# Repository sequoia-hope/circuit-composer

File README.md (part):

# circuit-composer

Board design as composition: chips are ingested once into verified, published packages, and
boards are built by combining them. It covers the stage between schematic and routing:
constraint definition and physical design planning. The full design is in
[`Circuit Composer — System Spec.md`](Circuit%20Composer%20—%20System%20Spec.md).

It sits between two sibling projects:

- **[Boardroom](../boardroom)** (formerly easy_pcb) runs a board from requirements to fab outputs with the
  `pcb-design` skill. Its phase-3 classification (`design/nets.csv`) imports into an intent file,
  and its worked example, easy2350, is the first annotated board here.
- **[ultraroute](../ultraroute)** is the router. It takes this project's output: a KiCad board
  with critical blocks placed, routed and locked, plus rules and cost grids.

## Status

- **Milestone 1, intent schema v0:** done. Rust types, a generated JSON Schema, a validator,
  and one real board annotated by hand (`boards/easy2350/`) that passes it.
- **Milestone 2, one buck end to end:** done, for the RP2350's core regulator, an on-chip buck
  with an external inductor and capacitors. That covers a generator, fast-tier verifier checks,
  a comparison against Raspberry Pi's reference layout, and the first package,
  `packages/rp2350` 0.1.0, published in this repository.
- **Milestone 3, router integration:** done on our side. The constraint compiler, the region
  check and a routed-board seam check are in place. easy2350, with its blocks locked, was routed
  by ultraroute and passes every check (`boards/easy2350/routed/`), with and without
  ultraroute's `--regions` reading the compiled regions.
- **Milestone 4, RP2350 package:** `packages/rp2350` 0.2.0. Core-regulator layouts for QFN-60
  and QFN-80 on 2 and 4 layers, all beating Raspberry Pi's on the same checker. Crystal, USB,
  QSPI flash, buttons and decoupling as intent blocks, mined from the design guide and both
  minimal boards. Pin tables for both variants, 27 cited rules (disputes kept), and the support
  parts by role. `ccomp check package` judges any board against the package by role. Both
  reference boards pass every hard check. easy2350 fails one: its USB pair runs over the
  +3V3 plane, not ground.
- **Milestone 5, floorplanner and composer:** in progress.
  - **Composer:** `ccomp compose` builds a board's circuit from package instances, the board's
    own parts and the nets joining them, with a binding per instance for `ccomp check package`.
    Recomposing the RP2350A minimal board (55 nets) and easy2350 (65) reproduces their netlists
    exactly.
  - **Packages:** three more, each ingested from its datasheet with cited rules: `mcp73831`
    (LiPo charger), `tlv62569` (2 A buck, with a buck intent block) and `lsm6dso` (IMU); and
    the bolt earring's chips, as that board wires them: `lgs4056h` (charger), `ncp730` (3.3 V
    LDO), `tps22913` (load switch), `usblc6` (USB ESD) and `lsm6ds3trc` (IMU). And the RP2350
    motor controller's (rev A), as that board wires them: `eg3113` (one half-bridge phase: the
    EGmicro gate driver with its BSC030N08NS5 MOSFETs, bootstrap and gate network; the datasheet
    is Chinese only, quoted in Chinese), `ina240` (inline phase current sensing across two 8 mΩ
    shunts) and `lm74700` (ideal diode with its MOSFET, USB VBUS into the motor bus).
  - **The bolt earring from blocks:** `boards/bolt-earring/compose.json` composes the whole
    board from those packages, the RP2350's, and recipes for its power path, power latch,
    button, long-press BOOTSEL reset, dividers, light sensor and LED zones. It equals the
    bolt's netlist net for net (192 nets, all 256 parts). `loose.json` leaves the MCU's pins to
    the pin solver, which places all 15 connections. The app's Circuit workspace solves and
    composes it in the browser, with the pins and recipe parameters editable, and the Board
    workspace floorplans the solved board as well as the drawn one.
  - **KiCad output:** `tools/compose_kicad.py` writes the schematic (a box per block, a net
    label per pin) and the board through easy_pcb's writer. ERC is clean, and the board's pad
    nets equal the composed nets.
  - **Floorplanner:** `ccomp floorplan` places every part by simulated annealing, using
    pad-to-pad wirelength, courtyard overlap, board area, block cohesion, decoupling hints,
    rigid generated layouts, connectors flush on an edge facing out, through-hole pads that
    block both sides, and separations taken from the packages' rules.
    - In easy2350's own outline it finds a legal placement with 13 % less wirelength than the
      person's (763 mm against 878; KiCad DRC: no courtyard, clearance or short findings), with
      the parts whose place is part of the design locked where the person put them: the headers,
      USB-C, SWD, the RP2350 and its core regulator, the buttons and the LEDs.
    - A footprint locked in the board (KiCad's lock) stays put: `ccomp floorplan` fixes it, and
      the app reads each part's lock from the board it opens and writes it back when it saves.
    - The demo board is in `boards/rp2350-battery/`: USB-C, a charger, load sharing, a buck,
      the RP2350 and an IMU. It composes and floorplans legally at 40 × 32 mm.
    - Regions in the spec hold blocks to the brief's floorplan: a `must` region keeps its
      blocks' and parts' courtyards inside a polygon, a `never` region keeps them out (with no
      members, every moving part but those it `except`s), on one side or both. Both are hard,
      like overlap: `ok` needs no region misses.
    - A rigid layout's tracks and vias keep other parts off them, as its parts do. A part keeps
      the margin from a side an edge connector sits flush on, and separations rise in weight
      through the anneal, like overlaps, so the end keeps them.
  - **Board intent:** `ccomp compose --intent` writes the composed board's intent file: each
    package's `intent.json` in board names (its nets found through their pins, its parts
    through the binding, blocks and domains named `INSTANCE/NAME`), nets two packages share
    merged to the stricter values, then the composition's own `intent` (board nets no package
    covers, a default for the rest). KiCad's net names, as `compose_kicad.py` labels them. The
    charger and IMU packages carry intent files now; the battery board's validates against its
    netlist, 42 of 42 nets.
  - **Routing composed boards:** `tools/prepare_route.py` gives a placed board its stack-up
    (4 layers), the fab rules, a net class per net from its intent, planes, a current-width rule
    where a net's current needs one (IPC-2221), and each rigid block's generated copper, locked.
    `tools/route_board.sh` runs it all from the composition through ultraroute to the seam
    checks. The battery board routes in under a minute with 0 DRC errors, 0 unconnected and 0
    region violations on 4 of 4 seeds (`boards/rp2350-battery/routed/`).
  - **Package rules as routing constraints:** `ccomp compile` turns the packages' block
    constraints into regions: `via_count <= 0` into a via rule, `unreferenced_length_mm <= 0`
    into keeping off layers with no ground beside them and off the voids in the ground fill
    beside the others. Hard constraints are `never`, soft ones a weighted `avoid`. `ccomp floorplan
    --intent` keeps a length-limited net's pins' box under 0.75 of its limit. Against the
    rp2350 package the battery board went from 22 fails of 63 (2 hard) to 13 to 15, with no
    hard fail on any of 4 seeds.
  - **Decoupling:** `prepare_route.py --composed` draws and locks each decoupling capacitor's stub
    to its pin, and the floorplanner leaves room for it: a `near` hint is measured from the
    part's pad on that net, and other courtyards across the line to the pin are priced. The
    battery board's decoupling fails went from 6 to 1 to 3.
  - **Off-chip bucks:** `ccomp gen buck` places a divider (`rfb_top`, `rfb_bot`, `cff` roles: FB
    runs clear of the switch node, the VOUT sense from COUT when it fits), takes the output net
    from the inductor, can return ground through the plane (`gnd_return_vias`), and searches
    behind the switch pin's row (`back`). The TLV62569's layout (`packages/tlv62569/layouts/`)
    measures 3.53 mm² hot loop and 11.05 mm² output loop, and the battery board uses it: package
    fails 9 to 13 of 63, none hard, on 4 seeds (ultraroute f179fcb, which reads `clear_under`:
    other nets' vias keep their plane holes from under a hard over-ground net).
  - **Crossings:** `ccomp floorplan` can price crossings between the straight pin lines of the
    nets a block keeps over ground (`planar` from the intent, `w_cross`, off by default). On the
    battery board it took the QSPI fails from 8.25 to 7.0 on average over four placements, but
    the crystal's from 1.25 to 3.5 (`boards/rp2350-battery/routed/README.md`).
  - **Not yet:** room for every stub beside the chip (8 of 10 fit); the flash's QSPI over ground
    (soft in the rp2350 package, so the router pays its price);
    intent for the remaining packages and the recipes; package schematic sheets.
- **Research library:** `library/` holds 143 cited claims from 41 vendor app notes, datasheets
  and articles, on five topics:
  - buck layout,
  - half-bridges and motor drivers,
  - crystal oscillators,
  - USB, return paths and decoupling,
  - CAN, connector protection and trace current.

  It is one database with the packages' rules. 17 disputes are kept as linked pairs, one of
  them against an rp2350 rule. Every quote is checked against its document
  (`library/README.md`).

## The app (prototype)

`app/` is Circuit Composer's own UI, specified in [`docs/app-spec.md`](docs/app-spec.md): a Rust
core compiled to WASM (`app/core`, the floorplanner and the board document) and a Svelte page
(`app/web`). It opens a board's floorplan; you drag, rotate and lock parts, and the floorplanner
anneals live in a worker in the page, from scratch or refining what is there. The Circuit
workspace shows the board as blocks and the nets between them. Shape builds the board's
outline: rectangles, circles, slots, polygons and generators (the bolt earring's is the first),
each added or cut away, with corner rounding, symmetry, holes, keep-outs and SVG/DXF import;
"Use as board outline" hands it to the floorplanner. The geometry is `crates/shape`, also behind
`ccomp shape`, and a board's `shape.json` reaches `ccomp floorplan` when its spec sets no
outline. It runs with no server: it opens the example boards that
`app/examples.sh` exports from `boards/` into the site. That is also how it runs on GitHub Pages,
where the site is the app alone: <https://sequoia-hope.github.io/circuit-composer/>.
Boards are drawn through a placeholder until `board-draw`, the renderer shared with UltraRoute
Studio, lands. AI fills, the terminal and the handoff to UltraRoute need the app's server, which
is next.

```sh
app/examples.sh     # export boards/ as the app's example boards (committed)
app/build.sh        # core to WASM, page to app/dist/
./serve.sh          # then open /app/dist/ on the project's registered port
```

URL parameters: `board=NAME`, `view=circuit|board|shape|copper|rules` (`ws=` in older links),
`embed=1` (for Boardroom's single-window mode: a slim bar of workspaces and, for a project's board,
Save, in place of the header; selection is posted to the parent window). On a touchscreen a finger
pans the board and two pinch to zoom. With a mouse or a finger, a press on a part selects it, and
only a selected, unlocked part moves, once dragged past a few pixels; Esc during a drag puts it
back.

## Build and run

```sh
cargo build --release
ccomp=target/release/ccomp

$ccomp schema -o schema/intent.schema.json             # regenerate the JSON Schema
$ccomp classes                                         # net class presets and block types
$ccomp netlist path/to/board.kicad_sch                 # the netlist as JSON (runs kicad-cli)
$ccomp validate boards/easy2350/intent.json            # pass/fail, findings per net and block
$ccomp resolve boards/easy2350/intent.json             # nets with preset defaults filled in
$ccomp import easy-pcb ../boardroom/examples/easy2350/design/nets.csv \
    --board easy2350 --netlist ../boardroom/examples/easy2350/hw/easy2350/a/easy2350.kicad_sch \
    -o draft.json                                      # draft intent from Boardroom
```

Any command can work on a board in a project instead of being given every path:
`--project DIR` (`-C`) and `--board NAME` (`-b`) fill in the inputs it was not given from the
board's files. Boards live under `compose/<board>/` in a Boardroom project and under
`boards/<board>/` here, each optionally with a `board.json` naming where its files are
(`crates/ccomp/src/project.rs`). Outputs are still written only with `-o`.

```sh
$ccomp boards                                          # this repository's boards
$ccomp -b rp2350-battery boards                        # one board's files, and which exist
$ccomp -b rp2350-battery compose                       # = compose boards/rp2350-battery/compose.json
$ccomp -C ../my-project floorplan --seed 2             # a project's only board
```

Milestone 2's tools:

```sh
# Fast-tier checks on a buck block, with a picture of what was measured
$ccomp check buck board.kicad_pcb --roles vin=U1.49,sw=U1.48,pgnd=U1.47,fb=U1.50,cin=C6,cout=C7,inductor=L1 --svg block.svg
$ccomp check buck board.kicad_pcb --intent boards/easy2350/intent.json --block core_reg

# Generate the block (parts and copper in the IC's frame); --defaults prints the parameters
$ccomp gen buck board.kicad_pcb --intent boards/easy2350/intent.json --block core_reg -o gen.json

# Generate, apply to a test bench with pcbnew, verify, and run KiCad's DRC
~/.claude/bin/reserve -c 8 -l "buck bench" -- python3 tools/bench_buck.py BOARD ROLES.json OUT_DIR
python3 tools/apply_layout.py BOARD gen.json ROLES.json -o OUT.kicad_pcb [--group NAME] [--fixture]
# A vendor board's own regulator copper (parts, pours, joining tracks and vias) as a layout
python3 tools/extract_layout.py REFERENCE.kicad_pcb ROLES.json -o layout.json --source rp2350a_minimal
# Any reviewed cluster with no generator (a half-bridge cell, a BGA's decoupler field, bottom-side
# members included) lifted from a board as a rigid layout, plus roles.json beside it
python3 tools/lift_layout.py BOARD.kicad_pcb --anchor U501 --parts Q501 Q502 C510 -o DIR/layout.json [--roles ROLES.json]
python3 tools/compare_buck.py packages/rp2350/layouts/qfn60-4layer/compare.spec.json OUT_DIR
```

Milestone 4 adds net-level measurements, for interface blocks:

```sh
# Pad-to-pad copper paths, track with no ground beside it, nearest decoupling per power pin
$ccomp measure board.kicad_pcb --spec packages/rp2350/reference/rp2350a_minimal/measure.spec.json
python3 tools/kicad_pins.py board.net U1 --rename SWD=SWDIO   # a part's pin table from a netlist

# A board against a package, by role: wiring, block constraints, length limits, part values
$ccomp check package board.kicad_pcb --package packages/rp2350 --binding boards/easy2350/rp2350.binding.json
```

Composing and floorplanning (milestone 5):

```sh
python3 tools/circuit_check.py packages/*/schematic/circuit.*.json --kicad 9   # symbols, footprints, pins
$ccomp pins boards/rp2350-battery/loose.json -o compose.json                  # pins solved; a regulator for each rail named under rails with none
$ccomp check supplies boards/rp2350-battery/compose.json                       # each rail's range, budget and feeds, judged
$ccomp compose boards/rp2350-battery/compose.json -o composed.json --intent intent.json   # + the board's intent
python3 tools/compose_kicad.py composed.json OUT_DIR --easy-pcb ../boardroom    # schematic, ERC, board
$ccomp floorplan OUT_DIR/BOARD.kicad_pcb --composed composed.json --spec boards/rp2350-battery/floorplan.json -o placement.json
$ccomp floorplan ... --evaluate PLACED.kicad_pcb                               # score a person's placement
python3 tools/apply_placement.py OUT_DIR/BOARD.kicad_pcb placement.json -o placed.kicad_pcb   # + KiCad DRC
python3 tools/prepare_route.py placed.kicad_pcb --intent intent.json --spec boards/rp2350-battery/floorplan.json \
    --pro OUT_DIR/BOARD.kicad_pro -o ROUTE_IN                                  # stack-up, rules, classes, planes, locked blocks
ULTRAROUTE=PATH tools/route_board.sh rp2350-battery OUT [SEED]                 # all of it, routed and checked
```

Recomposing an existing board:

```sh
$ccomp compose boards/easy2350/compose.json -o composed.json --bindings OUT_DIR   # circuit + bindings
python3 tools/package_circuit.py packages/rp2350 --board qfn60 --variant RP2350A --netlist REF.net --chip U1 --source rp2350a_minimal -o packages/rp2350/schematic/circuit.RP2350A.json
python3 tools/compose_from_netlist.py draft BOARD.net --instance mcu rp2350@0.2.0 RP2350A BINDING.json --keep-designators -o compose.json
python3 tools/compose_from_netlist.py compare BOARD.net composed.json --binding mcu BINDING.json
```

The research library:

```sh
$ccomp library check                                   # ids, sources, links, both sides of each dispute
$ccomp library query --scope circuit=buck --status contested
python3 tools/library_fetch.py && python3 tools/library_quotes.py   # documents, hashes, quotes
```

Every command prints one JSON result. Exit status: 0 success, 1 the input failed validation,
2 the command could not run.

## Layout

| Path | What |
|---|---|
| `crates/intent/` | The schema types (`model.rs`), class presets and block types (`presets.rs`), the KiCad netlist reader, the validator, the easy_pcb importer |
| `crates/ccomp/` | The command-line harness |
| `crates/pcb/` | A KiCad board as copper per net (read with ultraroute's `kicad-pcb`, pinned), geometry, and copper-path search |
| `crates/verify/` | Fast-tier verifier checks (`buck.rs`, `nets.rs`) and SVG drawings of what they measured |
| `crates/floorplan/` | The floorplanner: simulated annealing over part poses, rigid groups, regions, edges, separations |
| `crates/compose/` | The composer: package instances, the board's own parts and nets into one circuit, with a binding per instance |
| `crates/library/` | The research library: cited claims from `library/` and every package's `rules.json`, checked and queried as one database |
| `crates/blockgen/` | Block generators (`buck.rs`) and the layout format, in the anchor part's frame |
| `tools/` | pcbnew-side steps: apply a layout, the test bench, comparisons |
| `library/` | Claims by circuit class, their sources (URLs and hashes; documents cached, not committed) |
| `packages/<chip>/` | Published packages: manifest, intent, cited rules, layouts with verify reports |
| `schema/intent.schema.json` | Generated; a test fails if it is stale |
| `boards/<board>/` | One annotated board each: `intent.json`, `input/` (netlist snapshot), `validate.json` |
| `.claude/skills/circuit-composer/` | The Claude Code skill that drives `ccomp` |

## The intent file (v0)

A JSON sidecar keyed by KiCad net names (`/GPIO0`, `+3V3`) and reference designators. Every
constrained value is `{value, strength: hard|soft, weight (soft only), provenance}`, and a
provenance cites a key of `sources` with a locator (page, section, timestamp) and a kind:
`datasheet`, `expert`, `simulated`, `requirement` (the board's own budget), or `preset`.

Net classes are presets over attributes: a class names the attributes a net must state (`SWITCH`
needs `voltage` and `current`) and supplies soft defaults for the rest (aggressor `strong`). A
default never satisfies a requirement and can never be hard.

The validator refuses a board until every connected net has intent with its class's required
fields, every block has a library type and owns real parts (no part in two blocks), every hard
constraint (including `must`/`never` region rules and protection paths) has a provenance that
resolves to a source, protection-path pads lie on their net, and differential pairs name each
other.

## Decisions

| Decision | Why |
|---|---|
| Intent file is JSON (spec open question) | The schema is generated as JSON Schema from the Rust types; packages already use `intent.json`; serde refuses unknown fields, so typos fail loudly |
| `requirement` and `preset` provenance kinds, beyond the spec's datasheet/expert/simulated | Board budgets (500 mA USB) are the designer's claims, not a datasheet's; presets must be visibly weaker than evidence |
| `max_length` net attribute, beyond the spec's table | easy_pcb's `length_limit` is enforced today and the router needs it |
| Regions may be anchored to a part | Package rules ("cut layer 2 under the inductor's LX pad") are stated relative to parts, before placement exists |
| Boards keep a netlist snapshot in `input/` | Validation is reproducible without the sibling checkout, as ultraroute's `jobs/<board>/input/` |

## Milestone 2: the RP2350 core regulator

**Checks** (`crates/verify/src/buck.rs`, about 1 s on a whole board). Copper paths are found
through tracks, vias and zone fills. Loop areas integrate |winding number|, so a loop that
crosses itself counts both lobes; a plain shoelace sum let them cancel and under-reported the
reference's output loop by half.

| Check | What |
|---|---|
| `hot_loop_area_mm2` | VIN pin → CIN → PGND pin along the copper |
| `output_loop_area_mm2` | SW pin → inductor → COUT → PGND pin |
| `switch_node_area_mm2` | All switch-net copper, overlaps counted once |
| `feedback_clearance_mm` | Feedback path (FB pin to COUT) to switch-node copper, IC pins excluded |
| `switch_node_underlap_mm2` | Other nets' copper on the layer under the switch node |

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
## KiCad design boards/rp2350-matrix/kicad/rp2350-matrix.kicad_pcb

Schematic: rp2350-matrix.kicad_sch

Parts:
C1, C2, C20: 10u; C_0805_2012Metric; Mpn CL21A106KAYNNNE; LCSC C15850
C3, C8: 4.7u; C_0402_1005Metric
C4, C7: 4.7u; C_0402_1005Metric_small_pads
C5, C6: 15p; C_0402_1005Metric
C9, C10, C11, C12, C13, C14, C15, C16, C17, C18: 100n; C_0402_1005Metric
C19: 6.8p; C_0402_1005Metric; Mpn 0402CG6R8C500NT; LCSC C1576
C21: 22u; C_0805_2012Metric; Mpn CL21A226MAQNNNE; LCSC C45783
C101, C102, C103, C104, C105, C106, C107, C108, C109, C110, C111, C112, C113, C114, C115, C116: 100n; C_0402_1005Metric; Mpn CL05B104KO5NNNC; LCSC C1525
D1: RED; LED_0603_1608Metric; Mpn KT-0603R; LCSC C2286
D3: B5819W; D_SOD-123; LCSC C8598
J1: USB-C; USB_C_Receptacle_HRO_TYPE-C-31-M-12; LCSC C165948
J2: BATT; JST_PH_S2B-PH-SM4-TB_1x02-1MP_P2.00mm_Horizontal; LCSC C295747
J3: SWD; PinHeader_1x03_P2.54mm_Vertical
L1: 3.3u; L_pol_2016
L2: 2.2u; L_Sunlord_SWPA4020S; Mpn SMNR4020-2.2UH; LCSC C135262
LED1, LED2, LED3, LED4, LED5, LED6, LED7, LED8, LED9, LED10, LED11, LED12, LED13, LED14, LED15, LED16, LED17, LED18, LED19, LED20, LED21, LED22, LED23, LED24, LED25, LED26, LED27, LED28, LED29, LED30, LED31, LED32, LED33, LED34, LED35, LED36, LED37, LED38, LED39, LED40, LED41, LED42, LED43, LED44, LED45, LED46, LED47, LED48, LED49, LED50, LED51, LED52, LED53, LED54, LED55, LED56, LED57, LED58, LED59, LED60, LED61, LED62, LED63, LED64: WS2816C-1313; LED_WS2816C-1313; Mpn WS2816C-1313/4P; LCSC C42417612
Q1: AO3401A; SOT-23; LCSC C15127
Q2: BSS138W; SOT-323_SC-70; Mpn BSS138W-7-F-ES; LCSC C5224279
R1, R2: 5.1k; R_0402_1005Metric; LCSC C25905
R3: 100k; R_0402_1005Metric; LCSC C25741
R4: 4.7k; R_0402_1005Metric; Mpn 0402WGF4701TCE; LCSC C25900
R5: 1k; R_0402_1005Metric; Mpn 0402WGF1001TCE; LCSC C11702
R6: 470; R_0402_1005Metric; Mpn 0402WGF4700TCE; LCSC C25117
R7: 33; R_0402_1005Metric
R8, R10, R15: 1k; R_0402_1005Metric
R9, R12: DNF; R_0402_1005Metric
R11: 0; R_0402_1005Metric
R13, R14: 27; R_0402_1005Metric
R16: 100k; R_0402_1005Metric; Mpn 0402WGF1003TCE; LCSC C25741
R17: 453k; R_0402_1005Metric; Mpn 0402WGF4533TCE; LCSC C27009
R18: 1M; R_0402_1005Metric; Mpn 0402WGF1004TCE; LCSC C26083
SW1, SW2: SW_Push; SW_Push_1P1T_NO_Vertical_Wuerth_434133025816
U1: MCP73831T-2ACI/OT; SOT-23-5; Mpn MCP73831T-2ACI/OT; LCSC C424093
U2: W25Q128JVS; SOIC-8_5.3x5.3mm_P1.27mm
U3: RP2350_60QFN; RP2350-QFN-60-1EP_7x7_P0.4mm_EP3.4x3.4mm_ThermalVias
U4: TLV62569DBV; SOT-23-5; Mpn TLV62569DBVR; LCSC C141836
Y1: ABM8-272-T3; Crystal_SMD_3225-4Pin_3.2x2.5mm

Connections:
/CC1: J1.A5 (CC1), R1.1
/CC2: J1.B5 (CC2), R2.1
/LED_DATA: Q2.1 (G), U3.27 (GPIO16)
/LED_DIN: LED1.4 (DIN), Q2.3 (D), R5.2
/SWCLK: J3.1, U3.24 (SWCLK)
/SWDIO: J3.3, U3.25 (SWD)
/USB_D+: J1.A6 (D+), J1.B6 (D+), R14.1
/USB_D-: J1.A7 (D-), J1.B7 (D-), R13.1
/VBAT: C2.1, J2.1, Q1.3 (D), U1.3 (V_{BAT})
/chg_PROG: R4.1, U1.5 (PROG)
/chg_STAT: R6.2, U1.1 (STAT)
/chg_STAT_LED: D1.1 (K), R6.1
/leds_D1_DO: LED1.2 (DOUT), LED2.4 (DIN)
/leds_D2_DO: LED2.2 (DOUT), LED3.4 (DIN)
/leds_D3_DO: LED3.2 (DOUT), LED4.4 (DIN)
/leds_D4_DO: LED4.2 (DOUT), LED5.4 (DIN)
/leds_D5_DO: LED5.2 (DOUT), LED6.4 (DIN)
/leds_D6_DO: LED6.2 (DOUT), LED7.4 (DIN)
/leds_D7_DO: LED7.2 (DOUT), LED8.4 (DIN)
/leds_D8_DO: LED8.2 (DOUT), LED9.4 (DIN)
/leds_D9_DO: LED9.2 (DOUT), LED10.4 (DIN)
/leds_D10_DO: LED10.2 (DOUT), LED11.4 (DIN)
/leds_D11_DO: LED11.2 (DOUT), LED12.4 (DIN)
/leds_D12_DO: LED12.2 (DOUT), LED13.4 (DIN)
/leds_D13_DO: LED13.2 (DOUT), LED14.4 (DIN)
/leds_D14_DO: LED14.2 (DOUT), LED15.4 (DIN)
/leds_D15_DO: LED15.2 (DOUT), LED16.4 (DIN)
/leds_D16_DO: LED16.2 (DOUT), LED17.4 (DIN)
/leds_D17_DO: LED17.2 (DOUT), LED18.4 (DIN)
/leds_D18_DO: LED18.2 (DOUT), LED19.4 (DIN)
/leds_D19_DO: LED19.2 (DOUT), LED20.4 (DIN)
/leds_D20_DO: LED20.2 (DOUT), LED21.4 (DIN)
/leds_D21_DO: LED21.2 (DOUT), LED22.4 (DIN)
/leds_D22_DO: LED22.2 (DOUT), LED23.4 (DIN)
/leds_D23_DO: LED23.2 (DOUT), LED24.4 (DIN)
/leds_D24_DO: LED24.2 (DOUT), LED25.4 (DIN)
/leds_D25_DO: LED25.2 (DOUT), LED26.4 (DIN)
/leds_D26_DO: LED26.2 (DOUT), LED27.4 (DIN)
/leds_D27_DO: LED27.2 (DOUT), LED28.4 (DIN)
/leds_D28_DO: LED28.2 (DOUT), LED29.4 (DIN)
/leds_D29_DO: LED29.2 (DOUT), LED30.4 (DIN)
/leds_D30_DO: LED30.2 (DOUT), LED31.4 (DIN)
/leds_D31_DO: LED31.2 (DOUT), LED32.4 (DIN)
/leds_D32_DO: LED32.2 (DOUT), LED33.4 (DIN)
/leds_D33_DO: LED33.2 (DOUT), LED34.4 (DIN)
/leds_D34_DO: LED34.2 (DOUT), LED35.4 (DIN)
/leds_D35_DO: LED35.2 (DOUT), LED36.4 (DIN)
/leds_D36_DO: LED36.2 (DOUT), LED37.4 (DIN)
/leds_D37_DO: LED37.2 (DOUT), LED38.4 (DIN)
/leds_D38_DO: LED38.2 (DOUT), LED39.4 (DIN)
/leds_D39_DO: LED39.2 (DOUT), LED40.4 (DIN)
/leds_D40_DO: LED40.2 (DOUT), LED41.4 (DIN)
/leds_D41_DO: LED41.2 (DOUT), LED42.4 (DIN)
/leds_D42_DO: LED42.2 (DOUT), LED43.4 (DIN)
/leds_D43_DO: LED43.2 (DOUT), LED44.4 (DIN)
/leds_D44_DO: LED44.2 (DOUT), LED45.4 (DIN)
/leds_D45_DO: LED45.2 (DOUT), LED46.4 (DIN)
/leds_D46_DO: LED46.2 (DOUT), LED47.4 (DIN)
/leds_D47_DO: LED47.2 (DOUT), LED48.4 (DIN)
/leds_D48_DO: LED48.2 (DOUT), LED49.4 (DIN)
/leds_D49_DO: LED49.2 (DOUT), LED50.4 (DIN)
/leds_D50_DO: LED50.2 (DOUT), LED51.4 (DIN)
/leds_D51_DO: LED51.2 (DOUT), LED52.4 (DIN)
/leds_D52_DO: LED52.2 (DOUT), LED53.4 (DIN)
/leds_D53_DO: LED53.2 (DOUT), LED54.4 (DIN)
/leds_D54_DO: LED54.2 (DOUT), LED55.4 (DIN)
/leds_D55_DO: LED55.2 (DOUT), LED56.4 (DIN)
/leds_D56_DO: LED56.2 (DOUT), LED57.4 (DIN)
/leds_D57_DO: LED57.2 (DOUT), LED58.4 (DIN)
/leds_D58_DO: LED58.2 (DOUT), LED59.4 (DIN)
/leds_D59_DO: LED59.2 (DOUT), LED60.4 (DIN)
/leds_D60_DO: LED60.2 (DOUT), LED61.4 (DIN)
/leds_D61_DO: LED61.2 (DOUT), LED62.4 (DIN)
/leds_D62_DO: LED62.2 (DOUT), LED63.4 (DIN)
/leds_D63_DO: LED63.2 (DOUT), LED64.4 (DIN)
/mcu_FLASH_SS: R9.2, R11.2, R12.2, U2.1 (~CS)
/mcu_GPIO0: R9.1, U3.2 (GPIO0)
/mcu_N_R_RUN_1: R10.1, SW2.1
/mcu_QSPI_SCLK: U2.6 (CLK), U3.56 (QSPI_SCLK)
/mcu_QSPI_SD0: U2.5 (DI/IO_{0}), U3.57 (QSPI_SD0)
/mcu_QSPI_SD1: U2.2 (DO/IO_{1}), U3.59 (QSPI_SD1)
/mcu_QSPI_SD2: U2.3 (~WP/IO_{2}), U3.58 (QSPI_SD2)
/mcu_QSPI_SD3: U2.7 (~HOLD/~RESET/IO_{3}), U3.55 (QSPI_SD3)
/mcu_QSPI_SS: R8.1, R11.1, U3.60 (QSPI_SS)
/mcu_RUN: SW2.2, U3.26 (RUN)
/mcu_USB_DM_PIN: R13.2, U3.51 (USB_DM)
/mcu_USB_DP_PIN: R14.2, U3.52 (USB_DP)
/mcu_VREG_LX: L1.2, U3.48 (VREG_LX)
/mcu_XIN: C5.1, U3.21 (XIN), Y1.1
/mcu_XOUT: R15.1, U3.22 (XOUT)
/mcu_XOUT_XTAL: C6.1, R15.2, Y1.3
/mcu_~USB_BOOT: R8.2, SW1.2
/reg_EN: R18.2, U4.1 (EN)
/reg_FB: C19.2, R16.1, R17.2, U4.5 (FB)
/reg_SW: L2.1, U4.3 (SW)

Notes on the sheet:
chg: charger
chg: status_led
leds: parts
mcu: bootsel
mcu: core_reg
mcu: crystal
mcu: flash
mcu: mcu
mcu: reset
mcu: usb
reg: reg
shift: parts
Board parts

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
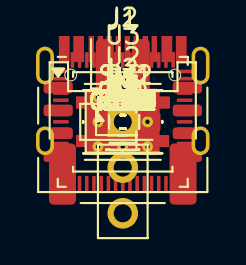
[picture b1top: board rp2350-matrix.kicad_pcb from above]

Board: 2 copper layers, 135 parts (0 on the bottom side), 101 nets, no tracks yet.

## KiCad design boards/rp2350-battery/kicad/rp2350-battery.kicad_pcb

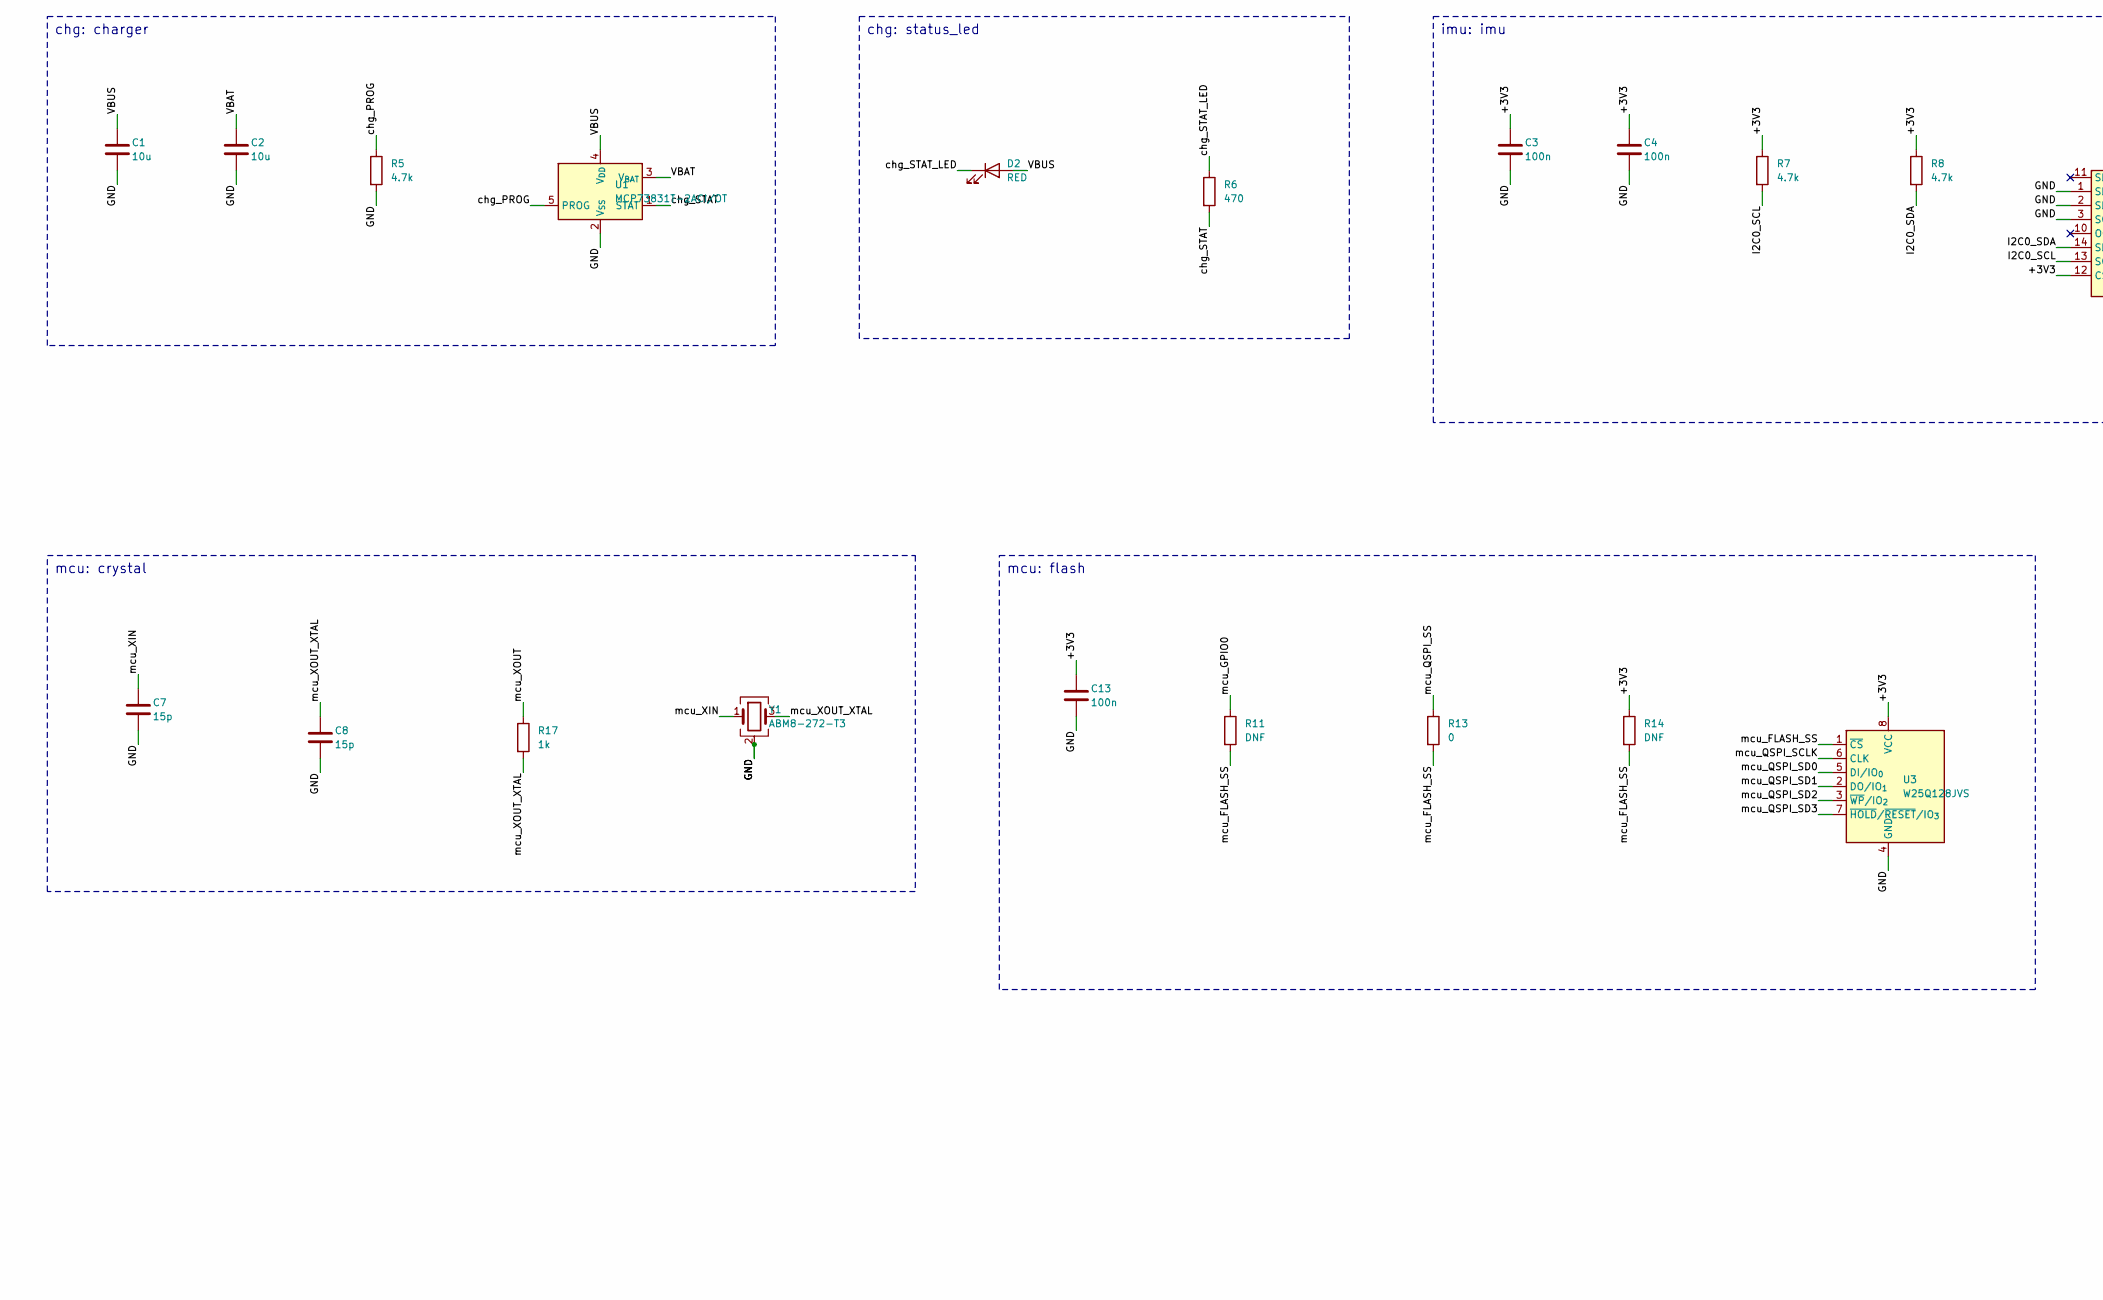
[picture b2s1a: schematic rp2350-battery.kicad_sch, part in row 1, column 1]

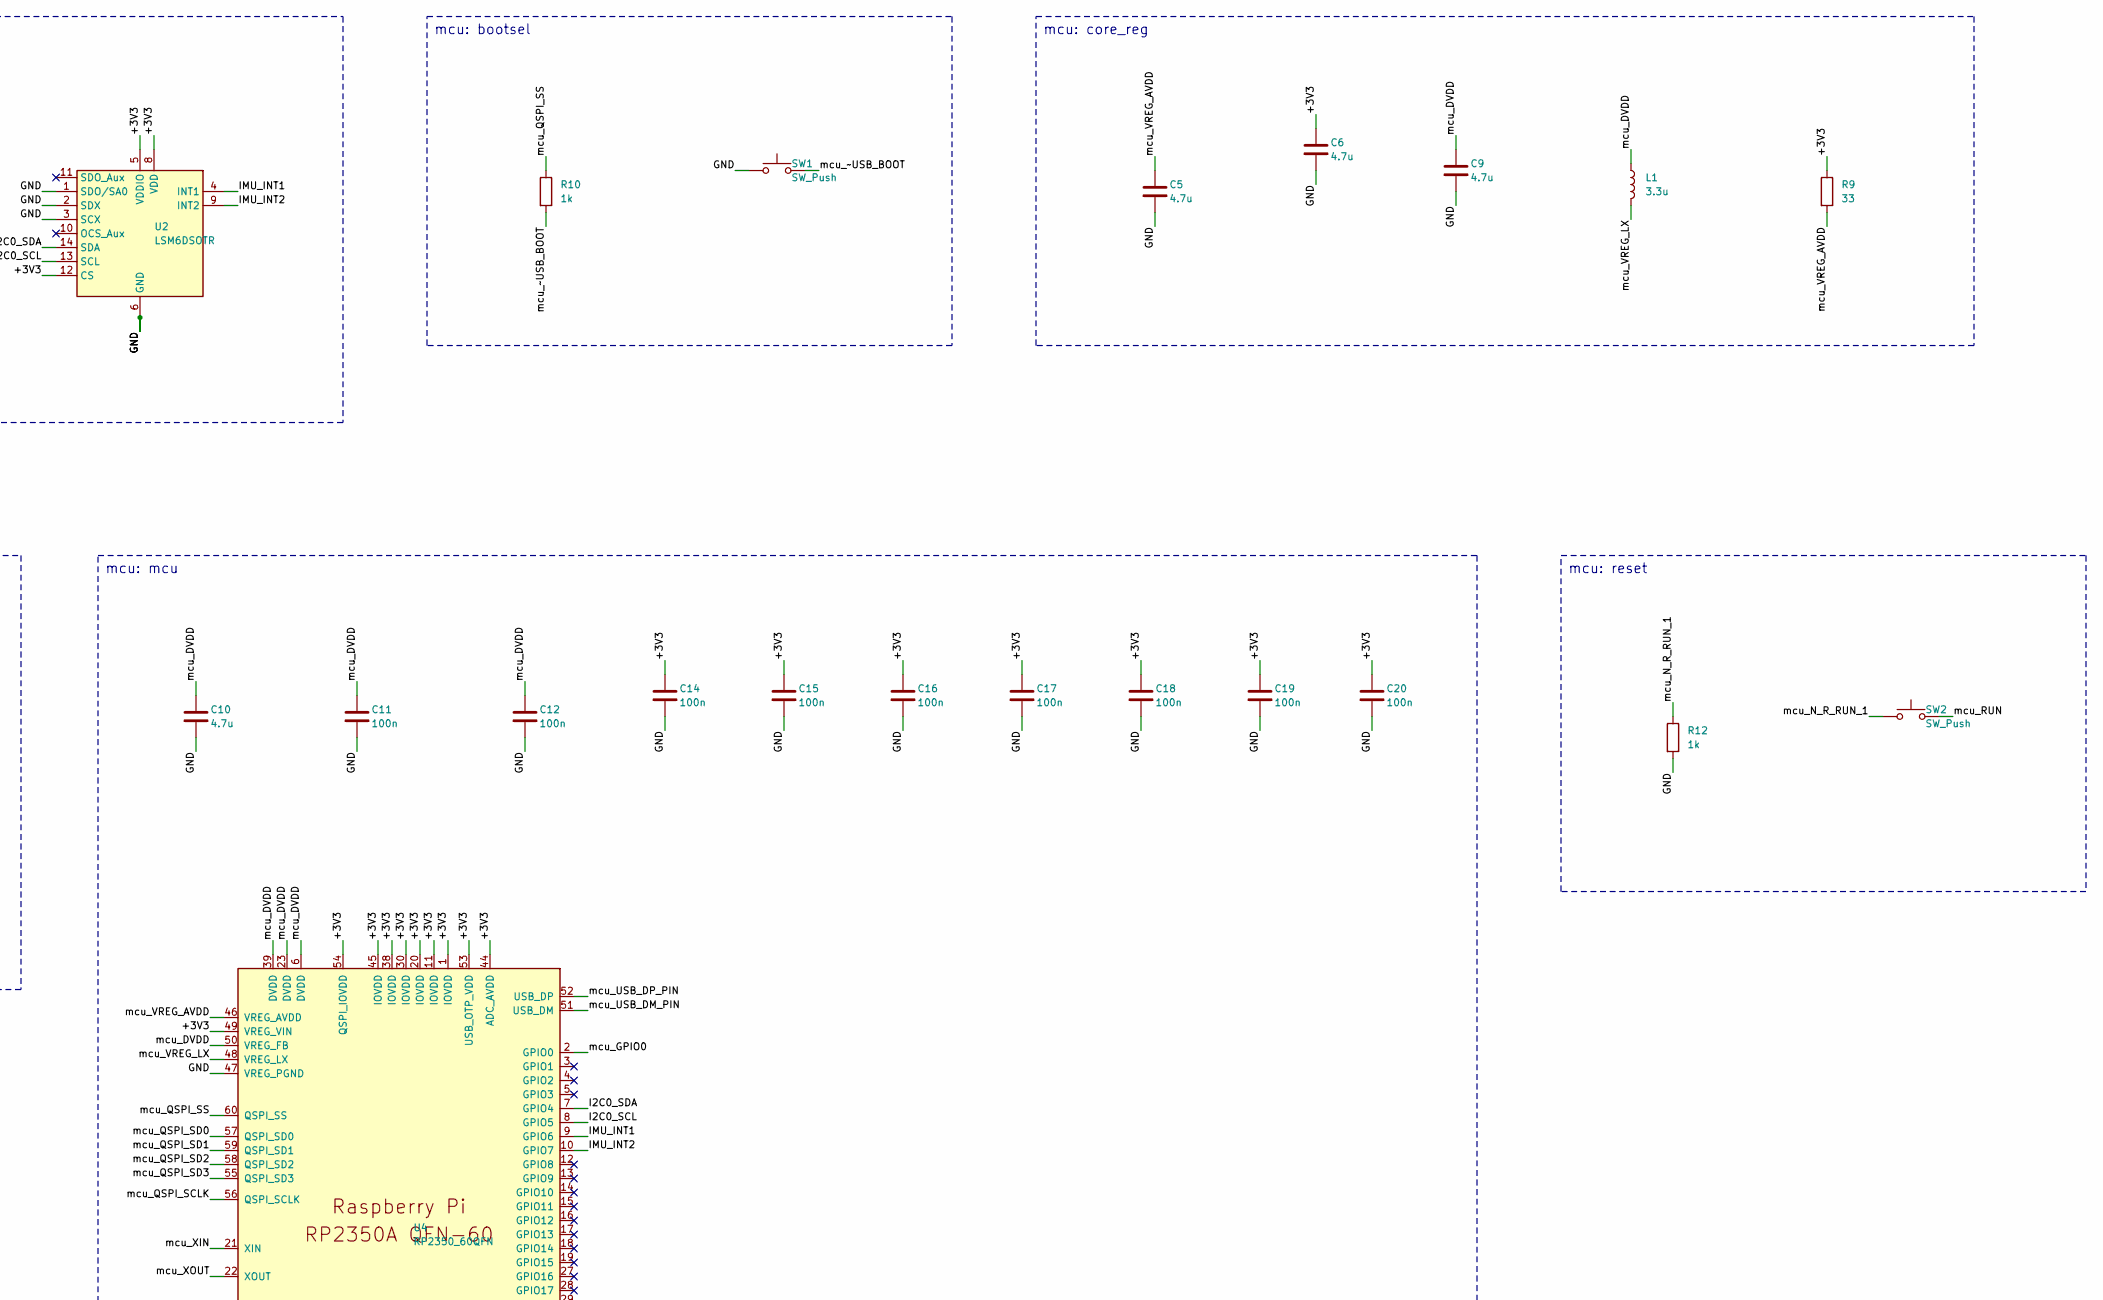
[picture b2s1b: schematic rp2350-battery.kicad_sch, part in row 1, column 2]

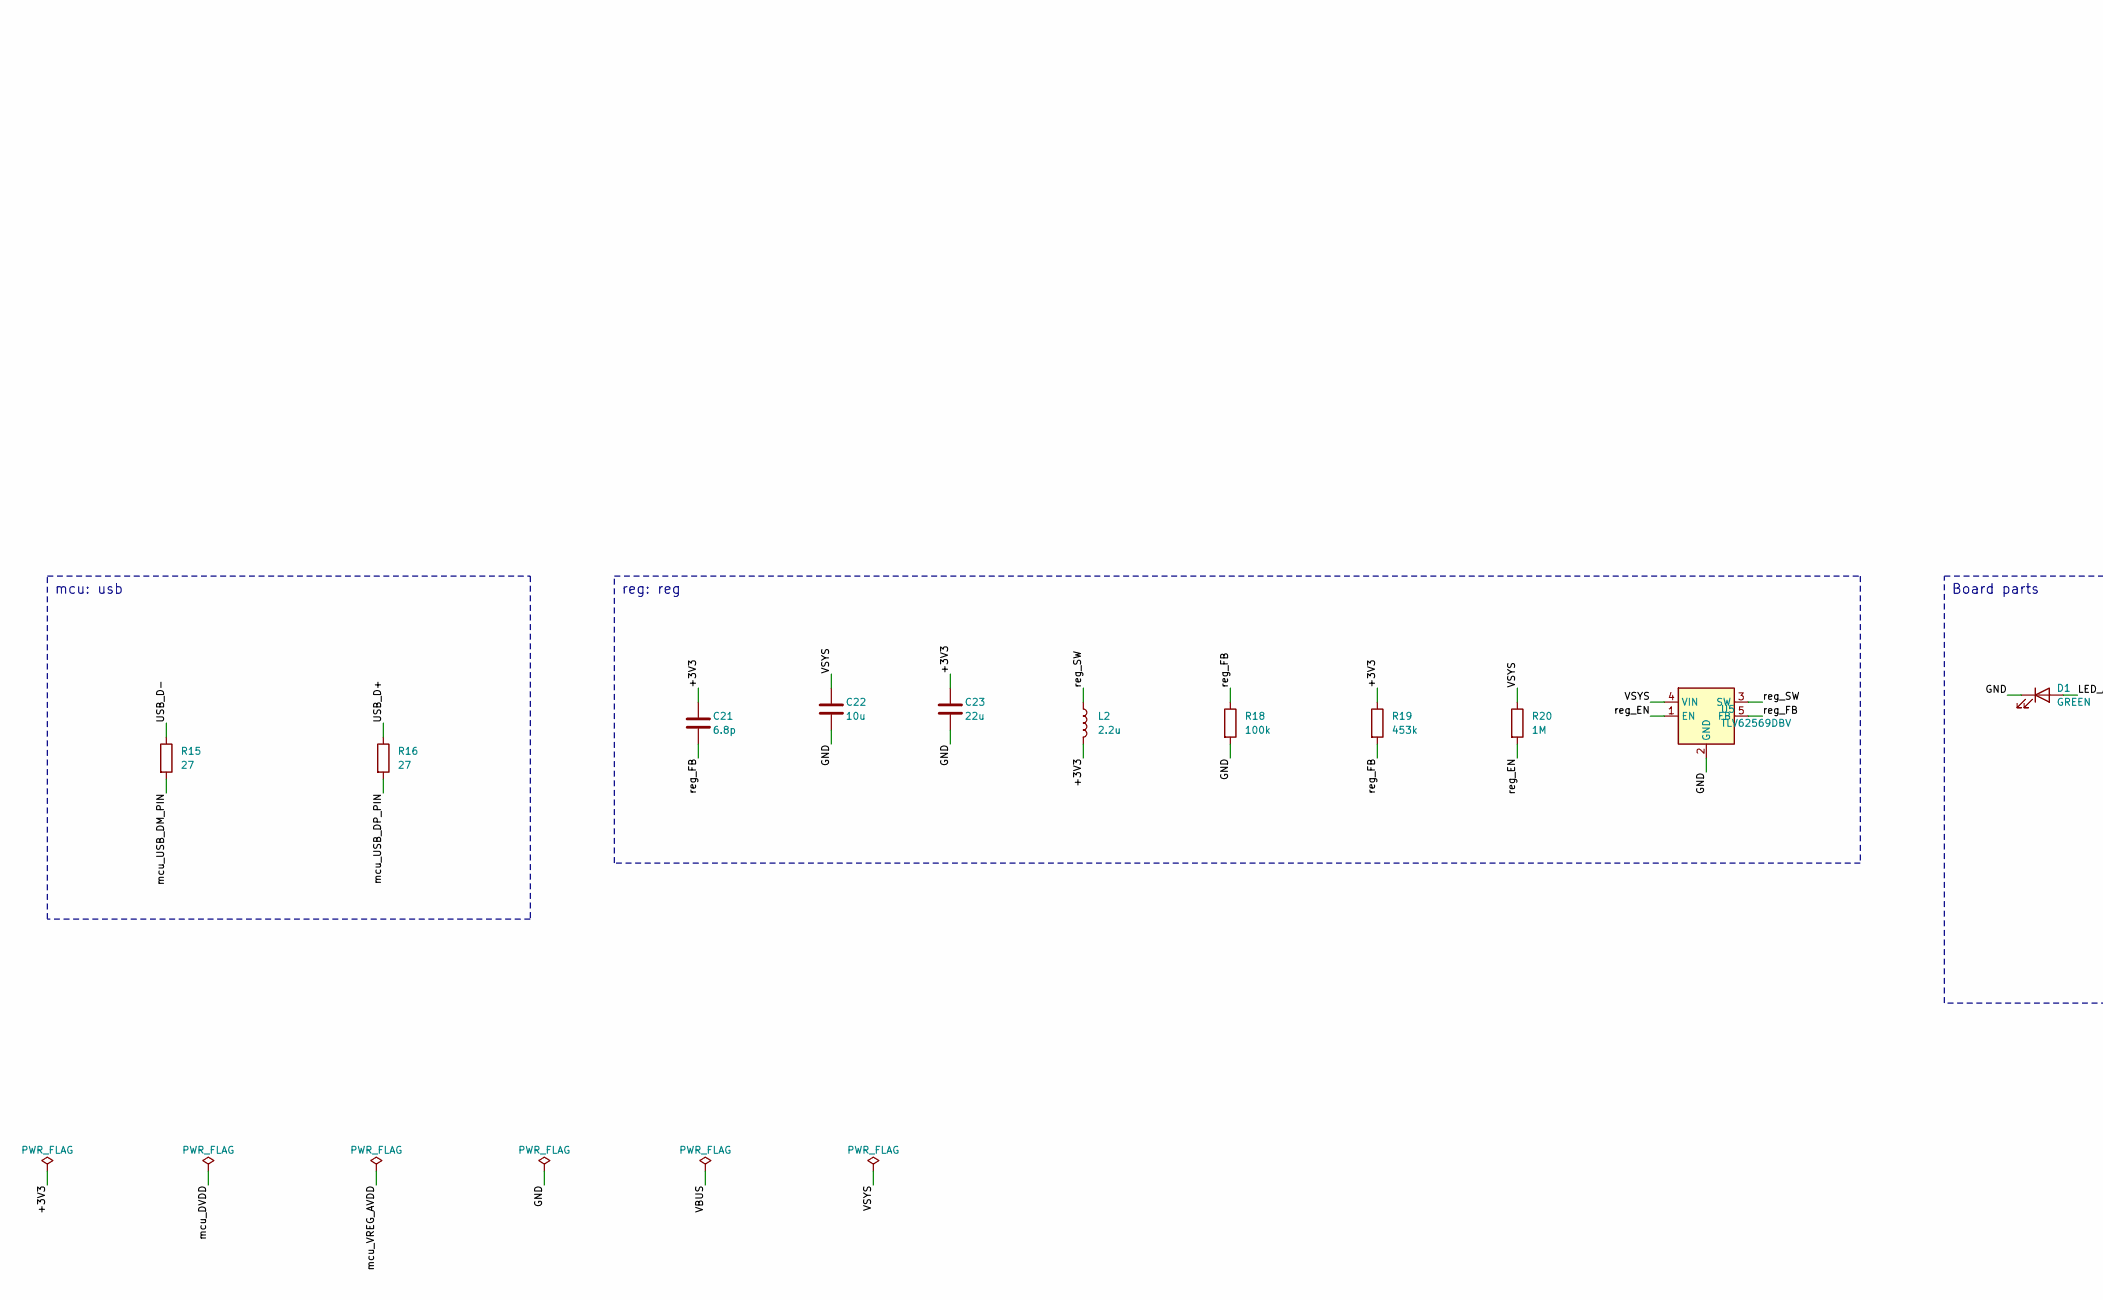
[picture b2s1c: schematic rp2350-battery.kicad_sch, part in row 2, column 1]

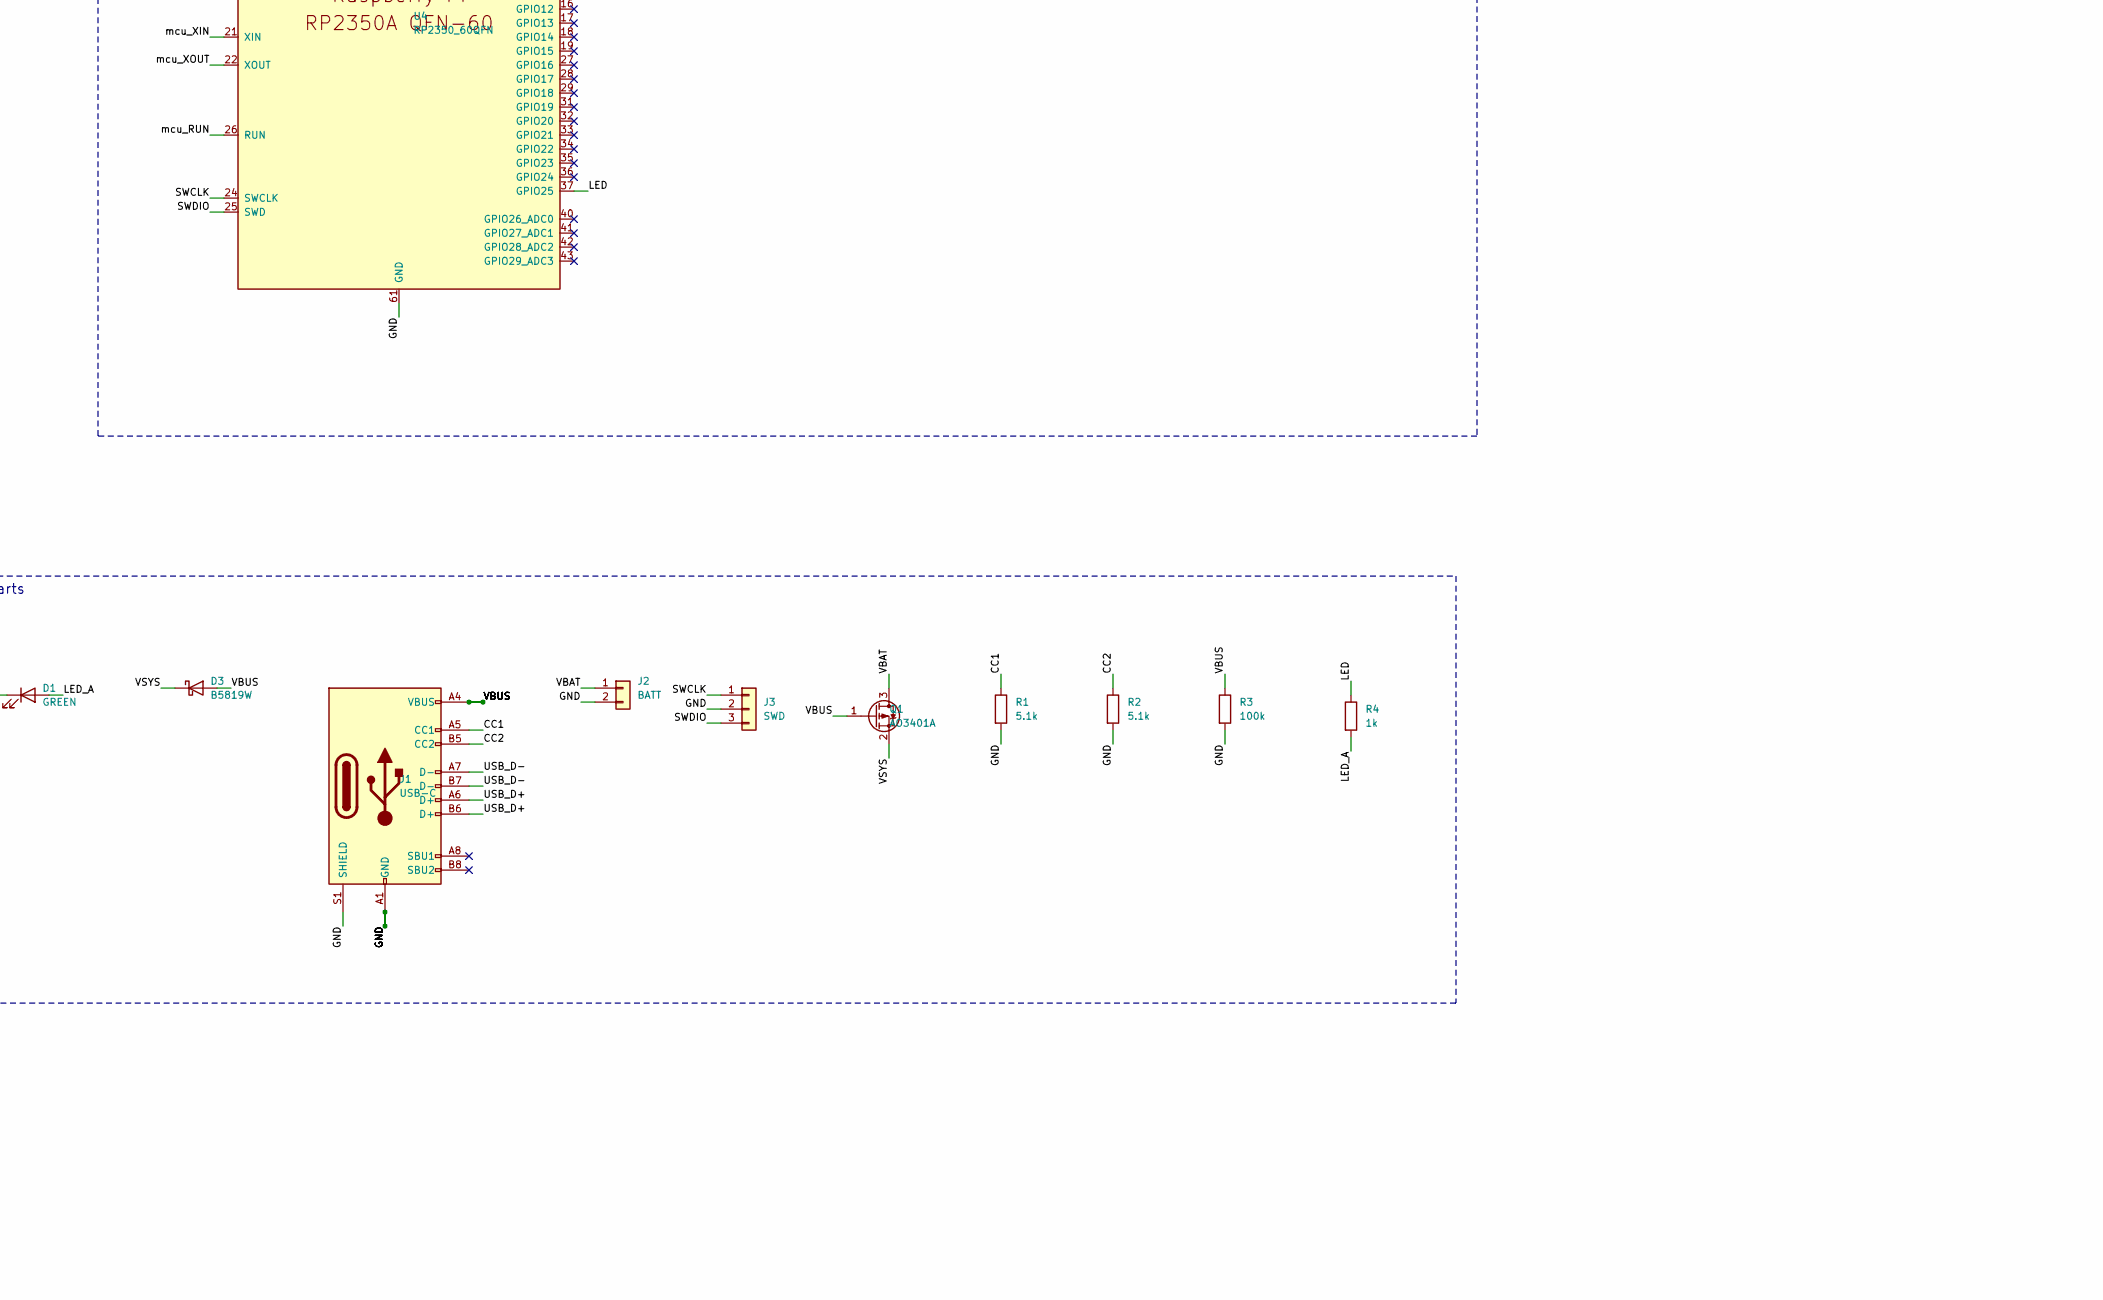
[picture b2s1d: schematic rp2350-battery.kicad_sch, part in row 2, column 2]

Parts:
C1, C2, C22: 10u; C_0805_2012Metric; Mpn CL21A106KAYNNNE; LCSC C15850
C3, C4: 100n; C_0402_1005Metric; Mpn CL05B104KO5NNNC; LCSC C1525
C5, C10: 4.7u; C_0402_1005Metric
C6, C9: 4.7u; C_0402_1005Metric_small_pads
C7, C8: 15p; C_0402_1005Metric
C11, C12, C13, C14, C15, C16, C17, C18, C19, C20: 100n; C_0402_1005Metric
C21: 6.8p; C_0402_1005Metric; Mpn 0402CG6R8C500NT; LCSC C1576
C23: 22u; C_0805_2012Metric; Mpn CL21A226MAQNNNE; LCSC C45783
D1: GREEN; LED_0603_1608Metric; LCSC C72043
D2: RED; LED_0603_1608Metric; Mpn KT-0603R; LCSC C2286
D3: B5819W; D_SOD-123; LCSC C8598
J1: USB-C; USB_C_Receptacle_HRO_TYPE-C-31-M-12; LCSC C165948
J2: BATT; JST_PH_S2B-PH-SM4-TB_1x02-1MP_P2.00mm_Horizontal; LCSC C295747
J3: SWD; PinHeader_1x03_P2.54mm_Vertical
L1: 3.3u; L_pol_2016
L2: 2.2u; L_Sunlord_SWPA4020S; Mpn SMNR4020-2.2UH; LCSC C135262
Q1: AO3401A; SOT-23; LCSC C15127
R1, R2: 5.1k; R_0402_1005Metric; LCSC C25905
R3: 100k; R_0402_1005Metric; LCSC C25741
R4: 1k; R_0402_1005Metric; LCSC C11702
R5, R7, R8: 4.7k; R_0402_1005Metric; Mpn 0402WGF4701TCE; LCSC C25900
R6: 470; R_0402_1005Metric; Mpn 0402WGF4700TCE; LCSC C25117
R9: 33; R_0402_1005Metric
R10, R12, R17: 1k; R_0402_1005Metric
R11, R14: DNF; R_0402_1005Metric
R13: 0; R_0402_1005Metric
R15, R16: 27; R_0402_1005Metric
R18: 100k; R_0402_1005Metric; Mpn 0402WGF1003TCE; LCSC C25741
R19: 453k; R_0402_1005Metric; Mpn 0402WGF4533TCE; LCSC C27009
R20: 1M; R_0402_1005Metric; Mpn 0402WGF1004TCE; LCSC C26083
SW1, SW2: SW_Push; SW_Push_1P1T_NO_Vertical_Wuerth_434133025816
U1: MCP73831T-2ACI/OT; SOT-23-5; Mpn MCP73831T-2ACI/OT; LCSC C424093
U2: LSM6DSOTR; LGA-14_3x2.5mm_P0.5mm_LayoutBorder3x4y; Mpn LSM6DSOTR; LCSC C2655100
U3: W25Q128JVS; SOIC-8_5.3x5.3mm_P1.27mm
U4: RP2350_60QFN; RP2350-QFN-60-1EP_7x7_P0.4mm_EP3.4x3.4mm_ThermalVias
U5: TLV62569DBV; SOT-23-5; Mpn TLV62569DBVR; LCSC C141836
Y1: ABM8-272-T3; Crystal_SMD_3225-4Pin_3.2x2.5mm

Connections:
/CC1: J1.A5 (CC1), R1.1
/CC2: J1.B5 (CC2), R2.1
/I2C0_SCL: R7.2, U2.13 (SCL), U4.8 (GPIO5)
/I2C0_SDA: R8.2, U2.14 (SDA), U4.7 (GPIO4)
/IMU_INT1: U2.4 (INT1), U4.9 (GPIO6)
/IMU_INT2: U2.9 (INT2), U4.10 (GPIO7)
/LED: R4.1, U4.37 (GPIO25)
/LED_A: D1.2 (A), R4.2
/SWCLK: J3.1, U4.24 (SWCLK)
/SWDIO: J3.3, U4.25 (SWD)
/USB_D+: J1.A6 (D+), J1.B6 (D+), R16.1
/USB_D-: J1.A7 (D-), J1.B7 (D-), R15.1
/VBAT: C2.1, J2.1, Q1.3 (D), U1.3 (V_{BAT})
/chg_PROG: R5.1, U1.5 (PROG)
/chg_STAT: R6.2, U1.1 (STAT)
/chg_STAT_LED: D2.1 (K), R6.1
/mcu_FLASH_SS: R11.2, R13.2, R14.2, U3.1 (~CS)
/mcu_GPIO0: R11.1, U4.2 (GPIO0)
/mcu_N_R_RUN_1: R12.1, SW2.1
/mcu_QSPI_SCLK: U3.6 (CLK), U4.56 (QSPI_SCLK)
/mcu_QSPI_SD0: U3.5 (DI/IO_{0}), U4.57 (QSPI_SD0)
/mcu_QSPI_SD1: U3.2 (DO/IO_{1}), U4.59 (QSPI_SD1)
/mcu_QSPI_SD2: U3.3 (~WP/IO_{2}), U4.58 (QSPI_SD2)
/mcu_QSPI_SD3: U3.7 (~HOLD/~RESET/IO_{3}), U4.55 (QSPI_SD3)
/mcu_QSPI_SS: R10.1, R13.1, U4.60 (QSPI_SS)
/mcu_RUN: SW2.2, U4.26 (RUN)
/mcu_USB_DM_PIN: R15.2, U4.51 (USB_DM)
/mcu_USB_DP_PIN: R16.2, U4.52 (USB_DP)
/mcu_VREG_LX: L1.2, U4.48 (VREG_LX)
/mcu_XIN: C7.1, U4.21 (XIN), Y1.1
/mcu_XOUT: R17.1, U4.22 (XOUT)
/mcu_XOUT_XTAL: C8.1, R17.2, Y1.3
/mcu_~USB_BOOT: R10.2, SW1.2
/reg_EN: R20.2, U5.1 (EN)
/reg_FB: C21.2, R18.1, R19.2, U5.5 (FB)
/reg_SW: L2.1, U5.3 (SW)

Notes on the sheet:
chg: charger
chg: status_led
imu: imu
mcu: bootsel
mcu: core_reg
mcu: crystal
mcu: flash
mcu: mcu
mcu: reset
mcu: usb
reg: reg
Board parts

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
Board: 2 copper layers, 60 parts (0 on the bottom side), 42 nets, no tracks yet.

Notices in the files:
README.md:
License:
MIT, see `LICENSE`. Packages are MIT too. They cite vendor documents by URL and hash and do not
include them. `compare/reference.*` are this project's measurements and drawings of Raspberry Pi's
published minimal-board layout, kept for comparison.
